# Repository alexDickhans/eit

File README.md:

# HIRO Group ERT Board V1

The name on the silkscreen is HIRO Group ERT Board V1. This board is a 16-electrode front end for a Raspberry Pi Pico W. J2 brings in the electrodes. Four analog switches connect those electrodes to a voltage measurement, a current source, and a current-return sense. A DAC and an op amp set the current. Two programmable-gain amplifiers and a two-channel ADC measure the voltage and the current. The Pico reads the ADC and sets the switch addresses and the gains.

Open `eit.kicad_pro` in KiCad 9. The schematic and the board were written by KiCad 9.0.

J2 is a 2×8 header, electrodes 0 through 15, with no electrode numbers on the silk. All four switches see the same electrodes. U6 selects the positive voltage electrode (its drain is `vin.+`, into U3). U8 selects the negative voltage electrode (`vin.?`, into U3). U11 selects the electrode that the current source drives (`current.out`). U10 selects the electrode that returns that current (`shunt.+`, into U4). Each switch enable pin is pulled to 3.3 V by a 10 k? resistor (R4 on U6, R13 on U8, R11 on U10, R12 on U11) and is not a Pico pin.

U9 is a 74HC595. Its serial input is Pico GPIO10, and its outputs address U10 and U11. U7 is the other 74HC595. Its serial input is GPIO11, and its outputs address U6 and U8. Both registers share SRCLK on GPIO13 and RCLK on GPIO12. Register clear is tied to 3.3 V, and output enable is tied to ground. Nothing has to be held at reset.

U3 and U4 are PGA281 amplifiers. U3 measures the electrode voltage. U4 measures the voltage across the 820 ? shunt R10. Both outputs go to U1, an ADS8354. Pico GPIO0 through GPIO4 set the U3 gain. GPIO5 through GPIO9 set the U4 gain.

U2 is a DAC80502. SPI2C (pin 5) and RSTSEL (pin 3) are tied to ground, so the part is in SPI mode. U5 is an OPA192. RN1 (four 100 k? resistors in one array) and RN2 (two 5 k? resistors in one array) are the resistors around that op amp. NT1 is a copper short from the ground end of R10 to GND. It is not a component.

## Pictures

Top of the board, USB edge up. The Pico (A1) is on the left and its USB connector faces the top edge. J1 is the 5-pin header just to the right of the Pico. J2 is the 16-pin header on the right. JP1 and JP2 are the open yellow solder jumpers near the top. U1, U5, U6, U8, U10, and U11 have no 3D model in the footprint, so those locations show the pads and the silkscreen outline. The Pico, the headers, the passives, D1, U2, U3, U4, U7, U9, RN1, and RN2 are the models from their footprints, sitting on the lands.

Bottom of the board, looking at the back, so left and right are swapped from the top photo. There are no parts on this side. The 2×8 set of holes on the left is J2. The five holes near the top are J1, and in this view the square pin-1 pad is the right-hand hole of that row. The four holes at the top right are the Pico USB shell holes.

Three-quarter view of the top, USB edge toward the lower left. The header pins and the Pico body are 3D models on their lands. The four empty outlines along the lower edge are U6, U8, U10, and U11, drawn as footprints because those packages have no 3D model. U1 and U5 are the same: pads and silk, not a package body.

Root sheet. The blocks are the power connector, the Pico, the current source, the voltage and current measurement, the switches, and J2.

Power sheet. J1 pins, in schematic order, are GND, +5V, +5VA, ?5VA, and +15V. R9 and R8 divide +5VA to make +2V5. The names GND, GNDA, and GNDD are one net.

Pico sheet. D1 is the MBR0540T1G from J1 +5V into VSYS. VBUS, RUN, and 3V3_EN are open.

Current source. U2, U5, RN1, RN2, the 820 ? shunt R10, the copper short NT1, and the open jumpers JP1 and JP2.

Measurement sheet. U3 is the voltage amplifier, U4 is the current amplifier, and U1 is the ADS8354.

Switch sheet. U6 is the positive voltage switch, U8 is the negative voltage switch, U11 is the current output, and U10 is the current return. U9 addresses U10 and U11. U7 addresses U6 and U8.

One switch, drawn for U6. U8, U10, and U11 use the same circuit. The drain (pin 28) is `vin.+` on U6, `vin.?` on U8, `shunt.+` on U10, and `current.out` on U11. S1 through S16 are electrodes 0 through 15.

Shift register U9. U7 is the same circuit, with serial data from GPIO11, and it drives U6 and U8.

J2 on the schematic. Pin 1 is electrode 7. On this drawing, pin 1 is at the bottom of the left column. On the board, pin 1 is the square pad at the top of the column closer to the middle of the board. The net is electrode 7 either way.

## Connectors and holes

Orient the board with the USB edge up, as in the top photo. There are no mounting holes and no test points. The boxes marked SN: and QC: are silkscreen only.

| Silk | What it is |
| --- | --- |
| J1 | 1×5 pin header, 2.54 mm. Power input. Pin 1 is the square pad, the left end. |
| J2 | 2×8 pin header, 2.54 mm. Electrodes. Pin 1 is the square pad at the top of the inner column (the column closer to the middle of the board). The silk does not number the electrodes. |
| JP1 | Open solder jumper. Left pad is GND, right pad is U2 VOUTB. Leave it open. Closing it shorts VOUTB to ground. |
| JP2 | Open solder jumper. Left pad is U2 VOUTA, right pad is GND. Leave it open. Closing it shorts VOUTA to ground. |
| A1 | Raspberry Pi Pico W. Pin 1 of the footprint is the left pin at the USB end (GPIO0). The USB connector faces the top edge. |
| D1 | SOD-123 diode. Pin 1 is the left end, the cathode band, on Pico VSYS. The right end is the anode, on J1 +5V. |
| D1, D2, D3 | Three 1.0 mm plated holes under the Pico footprint. They have no net. The module covers them once it is soldered. These are not the diode D1. |

J1, left to right. The silkscreen above the pins reads GND, +5V, +5VA, ?5VA, +15VA. The net on the last pin is +15V.

| J1 pin | Silkscreen | Net |
| --- | --- | --- |
| 1 | GND | GND |
| 2 | +5V | +5V |
| 3 | +5VA | +5VA |
| 4 | ?5VA | ?5VA |
| 5 | +15VA | +15V |

J2, with the USB edge up. The inner column is toward the middle of the board.

| Inner pin | Electrode | Outer pin | Electrode |
| --- | --- | --- | --- |
| 1 (top, square) | 7 | 2 | 15 |
| 3 | 6 | 4 | 14 |
| 5 | 5 | 6 | 13 |
| 7 | 4 | 8 | 12 |
| 9 | 3 | 10 | 11 |
| 11 | 2 | 12 | 10 |
| 13 | 1 | 14 | 9 |
| 15 (bottom) | 0 | 16 | 8 |

Pico pins that leave the module. Pin 1 is the top pin on the left edge.

| Pico pin | GPIO | Net |
| --- | --- | --- |
| 1 | GPIO0 | vgain0, U3 gain |
| 2 | GPIO1 | vgain1 |
| 4 | GPIO2 | vgain2 |
| 5 | GPIO3 | vgain3 |
| 6 | GPIO4 | vgain4 |
| 7 | GPIO5 | igain0, U4 gain |
| 9 | GPIO6 | igain1 |
| 10 | GPIO7 | igain2 |
| 11 | GPIO8 | igain3 |
| 12 | GPIO9 | igain4 |
| 14 | GPIO10 | U9 serial data |
| 15 | GPIO11 | U7 serial data |
| 16 | GPIO12 | shift-register RCLK |
| 17 | GPIO13 | shift-register SRCLK |
| 19 | GPIO14 | U2 chip select |
| 20 | GPIO15 | U1 chip select |
| 21 | GPIO16 | SPI MISO |
| 24 | GPIO18 | SPI clock |
| 25 | GPIO19 | SPI MOSI |
| 36 | 3V3 out | +3V3 |
| 39 | VSYS | cathode of D1 |
| 40 | VBUS | open |

GPIO17, GPIO20, GPIO21, GPIO22, GPIO26, GPIO27, GPIO28, ADC_VREF, RUN, and 3V3_EN are open on the board. The four holes beside the USB connector are non-plated holes in the Pico footprint (two 2.2 mm, two 1.85 mm) for the USB shell.

R4 and C38 are fitted. Their reference designators are hidden on the silkscreen, so the board does not print "R4" or "C38".

## Power

All board power comes in on J1. Pin 1, the square pad on the left, is ground. Supply +5V, +5VA, ?5VA, and +15V on the pins in the table above. +5VA is a separate pin from +5V. The board does not make one from the other.

There is no regulator, no charger, and no battery on this board. +3V3 is the Pico's own regulator, from VSYS, and it comes out on Pico pin 36. +2V5 is only the midpoint of R9 (10 k? from +5VA) and R8 (10 k? to GND). It is the output common-mode pin of U3 and U4. Do not use it to power anything.

D1 lets J1 +5V feed Pico VSYS and blocks the Pico from driving +5V back out of J1. The Pico USB connector does not power the Pico and does not power the analog rails, because VBUS is open. Plug in J1 +5V before expecting the Pico, the switches, or the ADC to run. +5VA, ?5VA, and +15V go straight to the analog parts, with no reverse protection. JP1 and JP2 must stay open.

## Manufacturing

Order a 6-layer, 1.6 mm board, 109.4 mm by 52.5 mm. Copper is 1 oz (0.035 mm) on every layer. F.Cu, In2.Cu, In3.Cu, and B.Cu are signal layers. In1.Cu and In4.Cu are ground planes. Mask is black and silk is white, as set in the stackup. The board file does not name a surface finish, and it does not call for impedance control.

The smallest trace is 0.15 mm, on F.Cu and In2.Cu. The smallest clearance in the design rules is 0.15 mm, on the electrode nets, and DRC reported no clearance errors. Vias are 0.6 mm pad / 0.3 mm drill, and 0.8 mm pad / 0.4 mm drill. Plated holes are 1.0 mm (J1, J2, and the three holes under the Pico) and one 0.20 mm hole in the U1 exposed pad. Non-plated holes are the four Pico USB shell holes. The copper-to-edge rule in the board is 0.5 mm, and DRC reported no edge violations.

Send `production/eit.zip`. It contains the six copper layers, both solder masks, both silkscreens, both paste layers, the board outline, and one Excellon drill file. Coordinates are absolute, in millimeters, and the soldermask is subtracted from the silk. The bottom paste file is empty because every part is on the top. The drill file includes the plated and the non-plated holes. Do not add a drill map or a separate non-plated drill file.

`production/bom.csv` is the parts list: Designator, Comment, Footprint, Qty, and LCSC Part #. Comment is the value printed in the schematic. JP1, JP2, and NT1 are left off on purpose. A1 has no LCSC number; buy a Raspberry Pi Pico W and fit it to the handsolder footprint. C6, C38, and C53 are 0.1 µF in 0402 under LCSC C1525. The other 0.1 µF 0402 parts are C343047. Both are 100 nF, 0402. RN1 is one 4-resistor array, 100 k? each (LCSC package 0603×4, footprint `R_Array_Convex_4x0612`). RN2 is one 2-resistor array, 5 k? each (LCSC package 0603×2, footprint `R_Array_Convex_2x0606`). R10 is an 820 ? resistor on a 0603 resistor footprint.

`production/position.csv` is the KiCad placement file for both sides, in millimeters. DNP parts are excluded, and so are JP1, JP2, NT1, and the two silk logos. The header is Designator, Val, Package, Mid X, Mid Y, Rotation, Layer. Y is negative, the same origin as the gerbers. Do not flip Y, and do not negate X. Every part is on the top, so the Layer column reads `top`. The rotations are KiCad's. Check the assembler's placement preview before paying.

Parts that are easy to rotate the wrong way, with the USB edge as the top edge:

| Part | Pin 1 |
| --- | --- |
| A1 Pico W | Left pin at the USB end. The USB connector faces the top edge. |
| D1 | Left end. That end is the cathode band, on VSYS. |
| J1 | Square pad, left end. |
| J2 | Square pad, top of the inner column. |
| U1 | Corner toward the bottom-left of the package. |
| U2 | Corner toward the bottom-right of the package. |
| U3 | Corner toward the top-left of the package. |
| U4 | Corner toward the top-right of the package. |
| U5 | Lower pin on the left side of the SOT-23. |
| U6, U8, U10, U11 | Bottom-left corner of each TSSOP. The silkscreen outline is the footprint, not a drawn module. |
| U7, U9 | Bottom-right corner of each SOIC. |
| RN1 | Left end, the pad closer to the USB edge. |
| RN2 | Pad closer to the USB edge. |

## Design files

| Path | What it is |
| --- | --- |
| `eit.kicad_pro` | KiCad 9 project |
| `eit.kicad_sch` | Root schematic. The other `.kicad_sch` files are the sheets. |
| `eit.kicad_pcb` | Board |
| `production/eit.zip` | Gerbers and drill for this revision |
| `production/bom.csv` | Bill of materials |
| `production/position.csv` | Placement, both sides, millimeters |
| `images/` | The pictures above |

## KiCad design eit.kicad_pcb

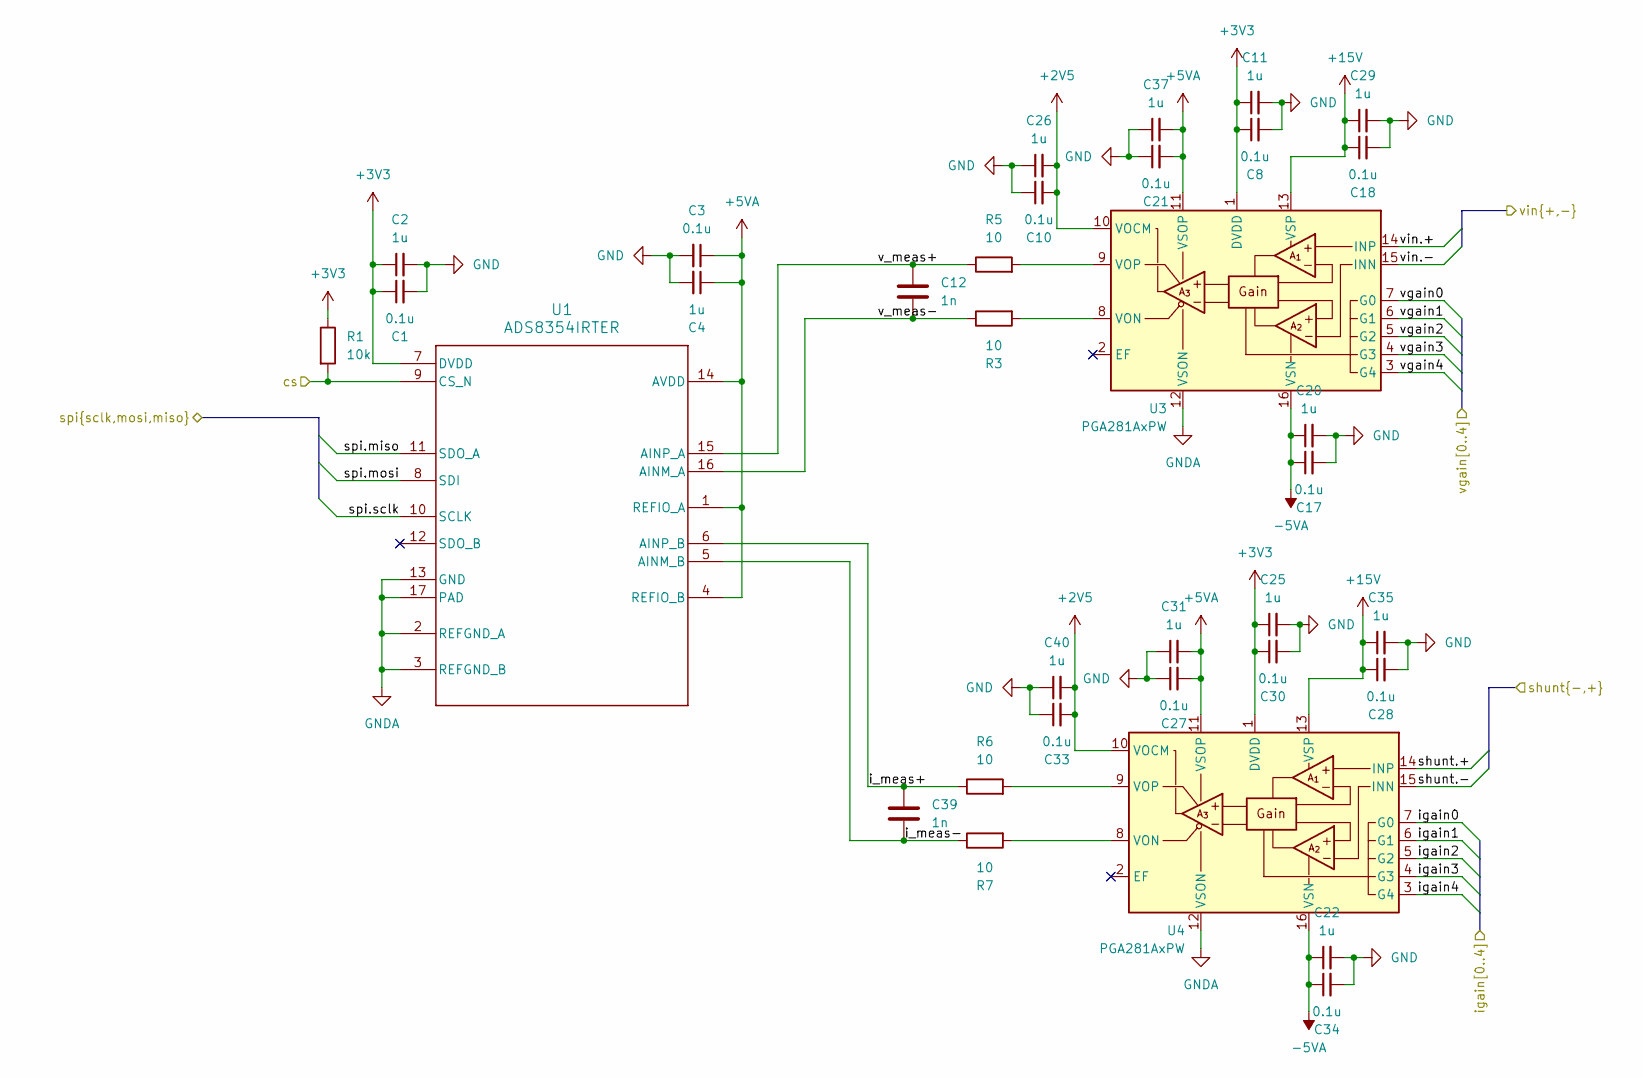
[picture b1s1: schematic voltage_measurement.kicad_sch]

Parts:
C1, C3, C8, C10, C17, C18, C21, C27, C28, C30, C33, C34: 0.1u; C_0402_1005Metric; LCSC Part # C343047
C2, C4, C11, C20, C22, C25, C26, C29, C31, C35, C37, C40: 1u; C_0603_1608Metric; LCSC Part # C342956
C12, C39: 1n; C_0402_1005Metric; LCSC Part # C1523
R1: 10k; R_0402_1005Metric; LCSC Part # C25744
R3, R5, R6, R7: 10; R_0402_1005Metric; LCSC Part # C25077
U1: ADS8354IRTER; RTE0016D; LCSC Part # C2670004
U3, U4: PGA281AxPW; TSSOP-16_4.4x5mm_P0.65mm; LCSC Part # C69359

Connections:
+2V5: C10.2, C26.2, C33.2, C40.2, U3.10 (VOCM), U4.10 (VOCM); also elsewhere on the board
+3V3: C1.1, C2.1, C8.1, C11.1, C25.1, C30.1, R1.1, U1.7 (DVDD), U3.1 (DVDD), U4.1 (DVDD); also elsewhere on the board
+5VA: C3.1, C4.1, C21.2, C27.2, C31.2, C37.2, U1.1 (REFIO_A), U1.4 (REFIO_B), U1.14 (AVDD), U3.11 (VSOP), U4.11 (VSOP); also elsewhere on the board
+15V: C18.1, C28.1, C29.1, C35.1, U3.13 (VSP), U4.13 (VSP); also elsewhere on the board
-5VA: C17.1, C20.1, C22.1, C34.1, U3.16 (VSN), U4.16 (VSN); also elsewhere on the board
/Current Injection/shunt.+: U4.14 (INP); also elsewhere on the board
/Current Injection/shunt.-: U4.15 (INN); also elsewhere on the board
/Current Injection/spi.miso: U1.11 (SDO_A); also elsewhere on the board
/Current Injection/spi.mosi: U1.8 (SDI); also elsewhere on the board
/Current Injection/spi.sclk: U1.10 (SCLK); also elsewhere on the board
/Microcontroller/adc_cs: R1.2, U1.9 (CS_N); also elsewhere on the board
/Microcontroller/igain0: U4.7 (G0); also elsewhere on the board
/Microcontroller/igain1: U4.6 (G1); also elsewhere on the board
/Microcontroller/igain2: U4.5 (G2); also elsewhere on the board
/Microcontroller/igain3: U4.4 (G3); also elsewhere on the board
/Microcontroller/igain4: U4.3 (G4); also elsewhere on the board
/Microcontroller/vgain0: U3.7 (G0); also elsewhere on the board
/Microcontroller/vgain1: U3.6 (G1); also elsewhere on the board
/Microcontroller/vgain2: U3.5 (G2); also elsewhere on the board
/Microcontroller/vgain3: U3.4 (G3); also elsewhere on the board
/Microcontroller/vgain4: U3.3 (G4); also elsewhere on the board
/Mux/vin.+: U3.14 (INP); also elsewhere on the board
/Mux/vin.-: U3.15 (INN); also elsewhere on the board
/Voltage Measurement/i_meas+: C39.1, R6.1, U1.6 (AINP_B)
/Voltage Measurement/i_meas-: C39.2, R7.1, U1.5 (AINM_B)
/Voltage Measurement/v_meas+: C12.1, R5.1, U1.15 (AINP_A)
/Voltage Measurement/v_meas-: C12.2, R3.1, U1.16 (AINM_A)
GND: C1.2, C2.2, C3.2, C4.2, C8.2, C10.1, C11.2, C17.2, C18.2, C20.2, C21.1, C22.2, C25.2, C26.1, C27.1, C28.2, C29.2, C30.2, C31.1, C33.1, C34.2, C35.2, C37.1, C40.1, U1.2 (REFGND_A), U1.3 (REFGND_B), U1.13 (GND), U1.17 (PAD), U3.12 (VSON), U4.12 (VSON); also elsewhere on the board
unnamed: R3.2, U3.8 (VON)
unnamed: R5.2, U3.9 (VOP)
unnamed: R7.2, U4.8 (VON)
unnamed: R6.2, U4.9 (VOP)

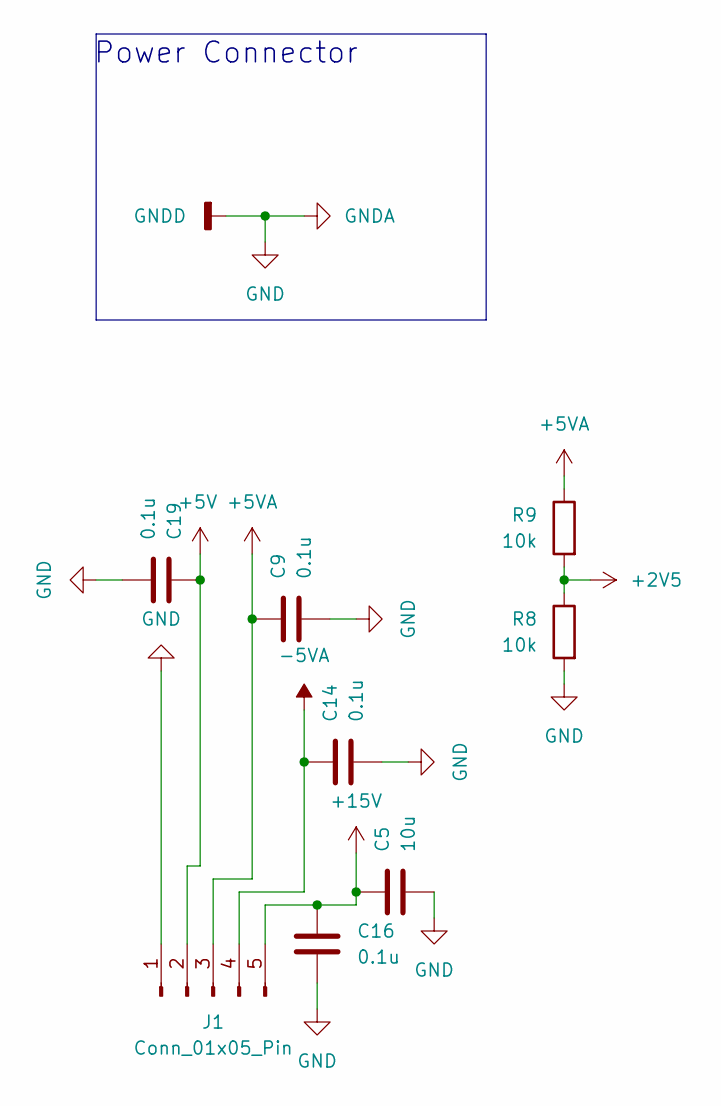
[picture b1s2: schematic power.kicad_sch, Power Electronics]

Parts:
C5: 10u; C_1210_3225Metric; LCSC Part # C18739
C9, C14, C16, C19: 0.1u; C_0603_1608Metric; LCSC Part # C14663
J1: Conn_01x05_Pin; PinHeader_1x05_P2.54mm_Vertical; LCSC Part # C188243
R8, R9: 10k; R_0402_1005Metric; LCSC Part # C25744

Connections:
+2V5: R8.1, R9.2; also elsewhere on the board
+5V: C19.2, J1.2; also elsewhere on the board
+5VA: C9.2, J1.3, R9.1; also elsewhere on the board
+15V: C5.1, C16.2, J1.5; also elsewhere on the board
-5VA: C14.2, J1.4; also elsewhere on the board
GND: C5.2, C9.1, C14.1, C16.1, C19.1, J1.1, R8.2; also elsewhere on the board

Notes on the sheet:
Power Connector

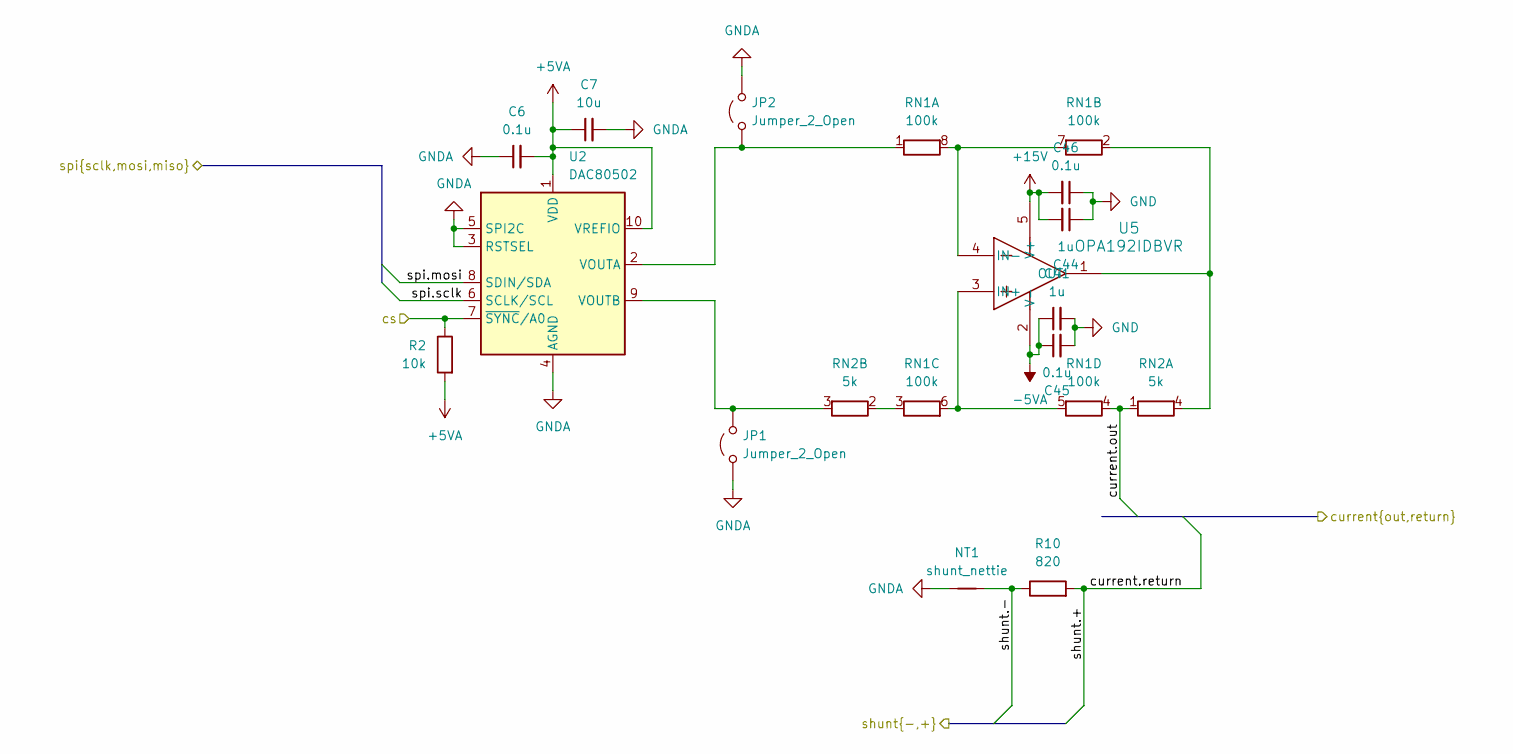
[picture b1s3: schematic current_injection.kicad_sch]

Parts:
C6: 0.1u; C_0402_1005Metric; LCSC Part # C1525
C7: 10u; C_0805_2012Metric; LCSC Part # C95841
C41, C44: 1u; C_0603_1608Metric; LCSC Part # C342956
C45, C46: 0.1u; C_0402_1005Metric; LCSC Part # C343047
JP1, JP2: Jumper_2_Open; SolderJumper-2_P1.3mm_Open_RoundedPad1.0x1.5mm
NT1: shunt_nettie; NetTie-2_SMD_Pad0.5mm
R2: 10k; R_0402_1005Metric; LCSC Part # C25744
R10: 820; R_0603_1608Metric; LCSC Part # C19700783
RN1: 100k; R_Array_Convex_4x0612; LCSC Part # C1731595
RN2: 5k; R_Array_Convex_2x0606; LCSC Part # C1731135
U2: DAC80502; Texas_DRX_WSON-10_2.5x2.5mm_P0.5mm; LCSC Part # C1880990
U5: OPA192IDBVR; DBV0005A_N; LCSC Part # C139648

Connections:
+5VA: C6.2, C7.1, R2.2, U2.1 (VDD), U2.10 (VREFIO); also elsewhere on the board
+15V: C44.2, C46.2, U5.5 (V+); also elsewhere on the board
-5VA: C41.1, C45.1, U5.2 (V-); also elsewhere on the board
/Current Injection/cs: R2.1, U2.7 (~SYNC/A0); also elsewhere on the board
/Current Injection/current.out: RN1.4 (R4.1), RN2.1 (R1.1); also elsewhere on the board
/Current Injection/shunt.+: R10.2; also elsewhere on the board
/Current Injection/shunt.-: NT1.2, R10.1; also elsewhere on the board
/Current Injection/spi.mosi: U2.8 (SDIN/SDA); also elsewhere on the board
/Current Injection/spi.sclk: U2.6 (SCLK/SCL); also elsewhere on the board
GND: C6.1, C7.2, C41.2, C44.1, C45.2, C46.1, JP1.1 (A), JP2.2 (B), NT1.1, U2.3 (RSTSEL), U2.4 (AGND), U2.5 (SPI2C); also elsewhere on the board
unnamed: JP1.2 (B), RN2.3 (R2.2), U2.9 (VOUTB)
unnamed: JP2.1 (A), RN1.1 (R1.1), U2.2 (VOUTA)
unnamed: RN1.7 (R2.2), RN1.8 (R1.2), U5.4 (IN-)
unnamed: RN1.2 (R2.1), RN2.4 (R1.2), U5.1 (OUT)
unnamed: RN1.3 (R3.1), RN2.2 (R2.1)
unnamed: RN1.5 (R4.2), RN1.6 (R3.2), U5.3 (IN+)

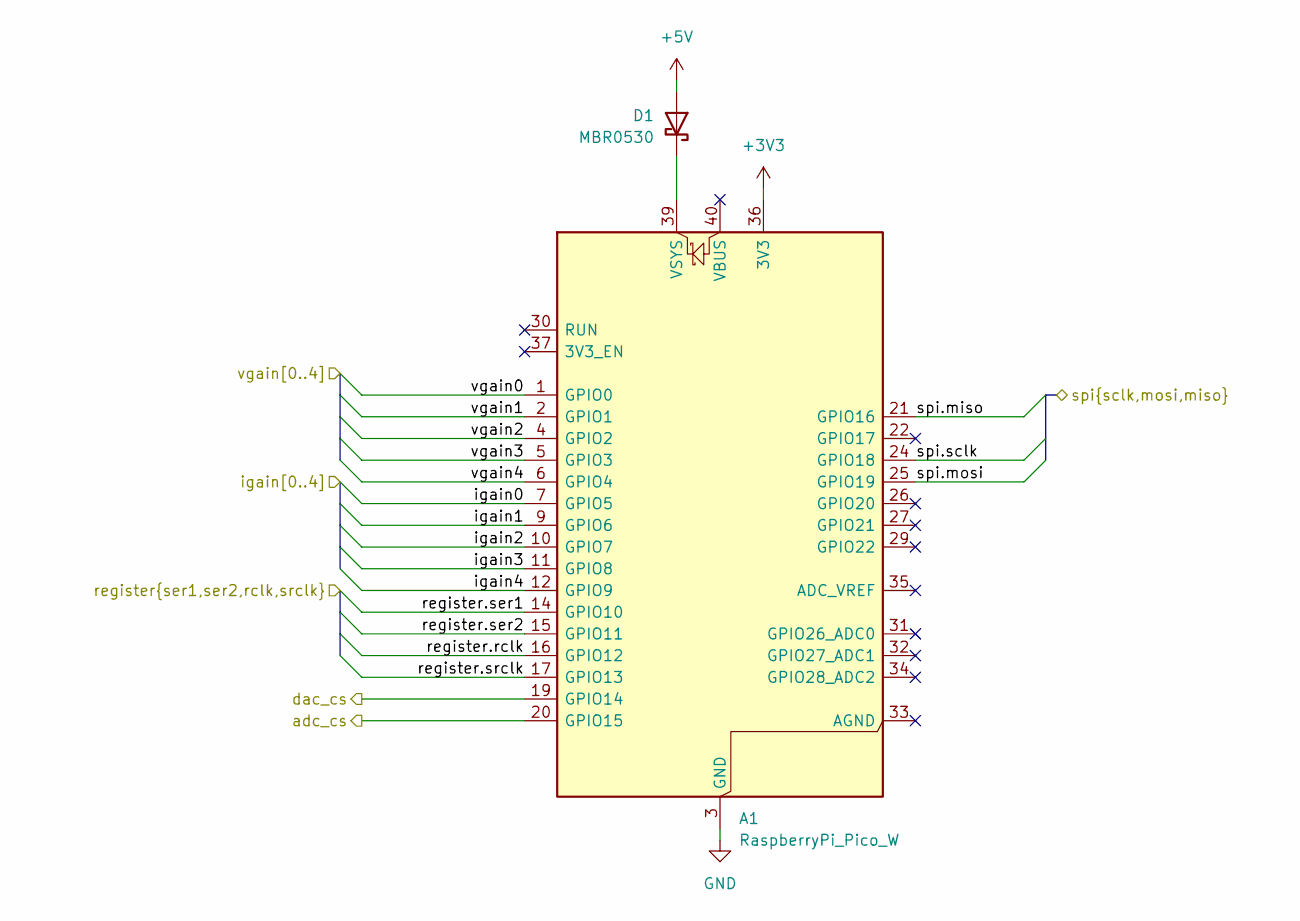
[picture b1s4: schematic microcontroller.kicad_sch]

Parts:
A1: RaspberryPi_Pico_W; RaspberryPi_Pico_W_SMD_HandSolder
D1: MBR0530; D_SOD-123; LCSC Part # C21353

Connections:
+3V3: A1.36 (3V3); also elsewhere on the board
+5V: D1.2 (A); also elsewhere on the board
/Current Injection/cs: A1.19 (GPIO14); also elsewhere on the board
/Current Injection/spi.miso: A1.21 (GPIO16); also elsewhere on the board
/Current Injection/spi.mosi: A1.25 (GPIO19); also elsewhere on the board
/Current Injection/spi.sclk: A1.24 (GPIO18); also elsewhere on the board
/Microcontroller/adc_cs: A1.20 (GPIO15); also elsewhere on the board
/Microcontroller/igain0: A1.7 (GPIO5); also elsewhere on the board
/Microcontroller/igain1: A1.9 (GPIO6); also elsewhere on the board
/Microcontroller/igain2: A1.10 (GPIO7); also elsewhere on the board
/Microcontroller/igain3: A1.11 (GPIO8); also elsewhere on the board
/Microcontroller/igain4: A1.12 (GPIO9); also elsewhere on the board
/Microcontroller/register.rclk: A1.16 (GPIO12); also elsewhere on the board
/Microcontroller/register.ser1: A1.14 (GPIO10); also elsewhere on the board
/Microcontroller/register.ser2: A1.15 (GPIO11); also elsewhere on the board
/Microcontroller/register.srclk: A1.17 (GPIO13); also elsewhere on the board
/Microcontroller/vgain0: A1.1 (GPIO0); also elsewhere on the board
/Microcontroller/vgain1: A1.2 (GPIO1); also elsewhere on the board
/Microcontroller/vgain2: A1.4 (GPIO2); also elsewhere on the board
/Microcontroller/vgain3: A1.5 (GPIO3); also elsewhere on the board
/Microcontroller/vgain4: A1.6 (GPIO4); also elsewhere on the board
GND: A1.3 (GND), A1.8 (GND), A1.13 (GND), A1.18 (GND), A1.23 (GND), A1.28 (GND), A1.38 (GND); also elsewhere on the board
unnamed: A1.39 (VSYS), D1.1 (K)

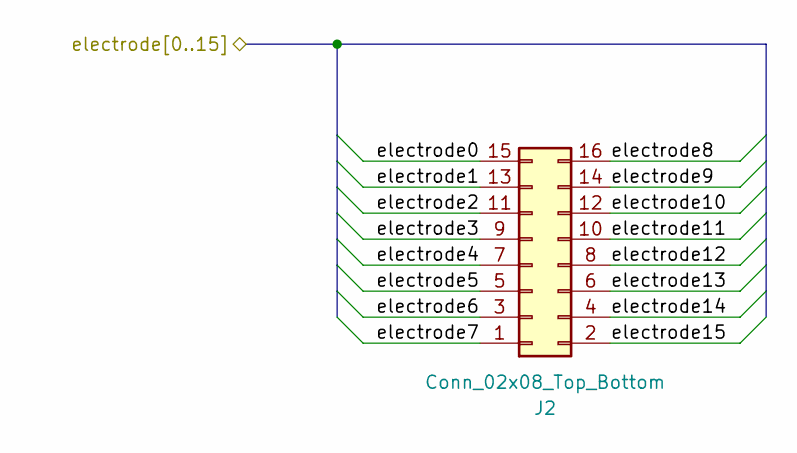
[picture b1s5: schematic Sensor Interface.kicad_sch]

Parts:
J2: Conn_02x08_Top_Bottom; PinHeader_2x08_P2.54mm_Vertical; LCSC Part # C68234

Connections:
/Mux/electrode0: J2.15; also elsewhere on the board
/Mux/electrode1: J2.13; also elsewhere on the board
/Mux/electrode2: J2.11; also elsewhere on the board
/Mux/electrode3: J2.9; also elsewhere on the board
/Mux/electrode4: J2.7; also elsewhere on the board
/Mux/electrode5: J2.5; also elsewhere on the board
/Mux/electrode6: J2.3; also elsewhere on the board
/Mux/electrode7: J2.1; also elsewhere on the board
/Mux/electrode8: J2.16; also elsewhere on the board
/Mux/electrode9: J2.14; also elsewhere on the board
/Mux/electrode10: J2.12; also elsewhere on the board
/Mux/electrode11: J2.10; also elsewhere on the board
/Mux/electrode12: J2.8; also elsewhere on the board
/Mux/electrode13: J2.6; also elsewhere on the board
/Mux/electrode14: J2.4; also elsewhere on the board
/Mux/electrode15: J2.2; also elsewhere on the board

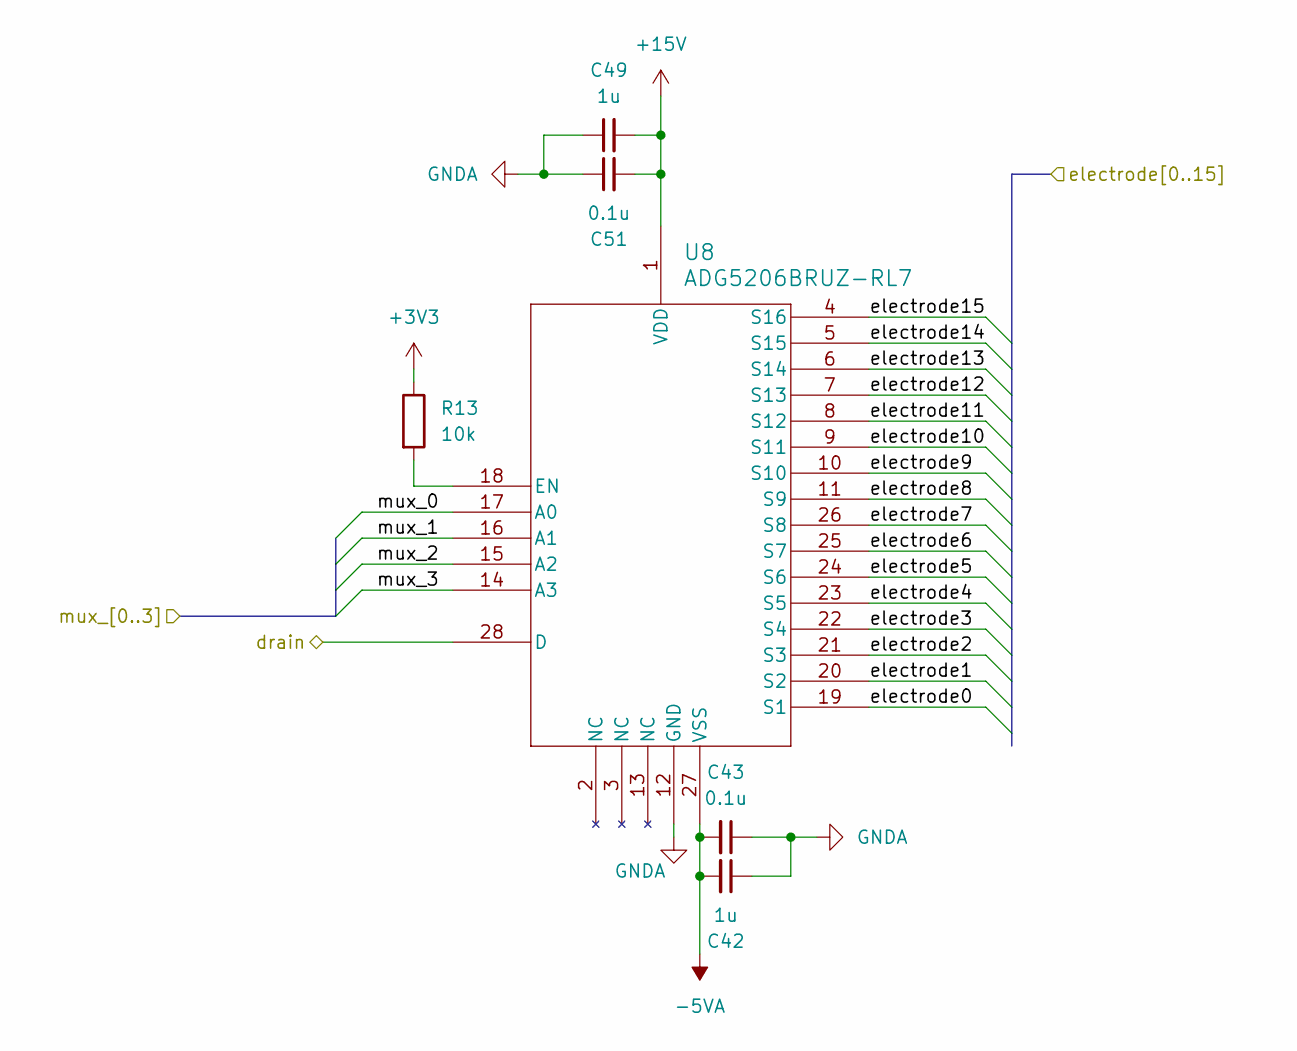
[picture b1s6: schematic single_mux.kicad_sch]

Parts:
C42, C49: 1u; C_0603_1608Metric; LCSC Part # C342956
C43, C51: 0.1u; C_0402_1005Metric; LCSC Part # C343047
R13: 10k; R_0402_1005Metric; LCSC Part # C25744
U8: ADG5206BRUZ-RL7; RU_28_ADI; LCSC Part # C657435

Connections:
+3V3: R13.1; also elsewhere on the board
+15V: C49.2, C51.2, U8.1 (VDD); also elsewhere on the board
-5VA: C42.2, C43.2, U8.27 (VSS); also elsewhere on the board
/Mux/Shift Register1/mux2_0: U8.17 (A0); also elsewhere on the board
/Mux/Shift Register1/mux2_1: U8.16 (A1); also elsewhere on the board
/Mux/Shift Register1/mux2_2: U8.15 (A2); also elsewhere on the board
/Mux/Shift Register1/mux2_3: U8.14 (A3); also elsewhere on the board
/Mux/electrode0: U8.19 (S1); also elsewhere on the board
/Mux/electrode1: U8.20 (S2); also elsewhere on the board
/Mux/electrode2: U8.21 (S3); also elsewhere on the board
/Mux/electrode3: U8.22 (S4); also elsewhere on the board
/Mux/electrode4: U8.23 (S5); also elsewhere on the board
/Mux/electrode5: U8.24 (S6); also elsewhere on the board
/Mux/electrode6: U8.25 (S7); also elsewhere on the board
/Mux/electrode7: U8.26 (S8); also elsewhere on the board
/Mux/electrode8: U8.11 (S9); also elsewhere on the board
/Mux/electrode9: U8.10 (S10); also elsewhere on the board
/Mux/electrode10: U8.9 (S11); also elsewhere on the board
/Mux/electrode11: U8.8 (S12); also elsewhere on the board
/Mux/electrode12: U8.7 (S13); also elsewhere on the board
/Mux/electrode13: U8.6 (S14); also elsewhere on the board
/Mux/electrode14: U8.5 (S15); also elsewhere on the board
/Mux/electrode15: U8.4 (S16); also elsewhere on the board
/Mux/vin.-: U8.28 (D); also elsewhere on the board
GND: C42.1, C43.1, C49.1, C51.1, U8.12 (GND); also elsewhere on the board
unnamed: R13.2, U8.18 (EN)

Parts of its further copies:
C13, C32, C36, C48, C52, C54: 0.1u; C_0402_1005Metric; LCSC Part # C343047
C15, C23, C24, C47, C50, C55: 1u; C_0603_1608Metric; LCSC Part # C342956
R4, R11, R12: 10k; R_0402_1005Metric; LCSC Part # C25744
U6, U10, U11: ADG5206BRUZ-RL7; RU_28_ADI; LCSC Part # C657435

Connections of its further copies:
+3V3: R4.1, R11.1, R12.1; also elsewhere on the board
+15V: C47.2, C48.2, C50.2, C52.2, C54.2, C55.2, U6.1 (VDD), U10.1 (VDD), U11.1 (VDD); also elsewhere on the board
-5VA: C13.2, C15.2, C23.2, C24.2, C32.2, C36.2, U6.27 (VSS), U10.27 (VSS), U11.27 (VSS); also elsewhere on the board
/Current Injection/current.out: U11.28 (D); also elsewhere on the board
/Current Injection/shunt.+: U10.28 (D); also elsewhere on the board
/Mux/Shift Register1/mux1_0: U6.17 (A0); also elsewhere on the board
/Mux/Shift Register1/mux1_1: U6.16 (A1); also elsewhere on the board
/Mux/Shift Register1/mux1_2: U6.15 (A2); also elsewhere on the board
/Mux/Shift Register1/mux1_3: U6.14 (A3); also elsewhere on the board
/Mux/Shift Register/mux1_0: U10.17 (A0); also elsewhere on the board
/Mux/Shift Register/mux1_1: U10.16 (A1); also elsewhere on the board
/Mux/Shift Register/mux1_2: U10.15 (A2); also elsewhere on the board
/Mux/Shift Register/mux1_3: U10.14 (A3); also elsewhere on the board
/Mux/Shift Register/mux2_0: U11.17 (A0); also elsewhere on the board
/Mux/Shift Register/mux2_1: U11.16 (A1); also elsewhere on the board
/Mux/Shift Register/mux2_2: U11.15 (A2); also elsewhere on the board
/Mux/Shift Register/mux2_3: U11.14 (A3); also elsewhere on the board
/Mux/electrode0: U6.19 (S1), U10.19 (S1), U11.19 (S1); also elsewhere on the board
/Mux/electrode1: U6.20 (S2), U10.20 (S2), U11.20 (S2); also elsewhere on the board
/Mux/electrode2: U6.21 (S3), U10.21 (S3), U11.21 (S3); also elsewhere on the board
/Mux/electrode3: U6.22 (S4), U10.22 (S4), U11.22 (S4); also elsewhere on the board
/Mux/electrode4: U6.23 (S5), U10.23 (S5), U11.23 (S5); also elsewhere on the board
/Mux/electrode5: U6.24 (S6), U10.24 (S6), U11.24 (S6); also elsewhere on the board
/Mux/electrode6: U6.25 (S7), U10.25 (S7), U11.25 (S7); also elsewhere on the board
/Mux/electrode7: U6.26 (S8), U10.26 (S8), U11.26 (S8); also elsewhere on the board
/Mux/electrode8: U6.11 (S9), U10.11 (S9), U11.11 (S9); also elsewhere on the board
/Mux/electrode9: U6.10 (S10), U10.10 (S10), U11.10 (S10); also elsewhere on the board
/Mux/electrode10: U6.9 (S11), U10.9 (S11), U11.9 (S11); also elsewhere on the board
/Mux/electrode11: U6.8 (S12), U10.8 (S12), U11.8 (S12); also elsewhere on the board
/Mux/electrode12: U6.7 (S13), U10.7 (S13), U11.7 (S13); also elsewhere on the board
/Mux/electrode13: U6.6 (S14), U10.6 (S14), U11.6 (S14); also elsewhere on the board
/Mux/electrode14: U6.5 (S15), U10.5 (S15), U11.5 (S15); also elsewhere on the board
/Mux/electrode15: U6.4 (S16), U10.4 (S16), U11.4 (S16); also elsewhere on the board
/Mux/vin.+: U6.28 (D); also elsewhere on the board
GND: C13.1, C15.1, C23.1, C24.1, C32.1, C36.1, C47.1, C48.1, C50.1, C52.1, C54.1, C55.1, U6.12 (GND), U10.12 (GND), U11.12 (GND); also elsewhere on the board
unnamed: R4.2, U6.18 (EN)
unnamed: R11.2, U10.18 (EN)
unnamed: R12.2, U11.18 (EN)

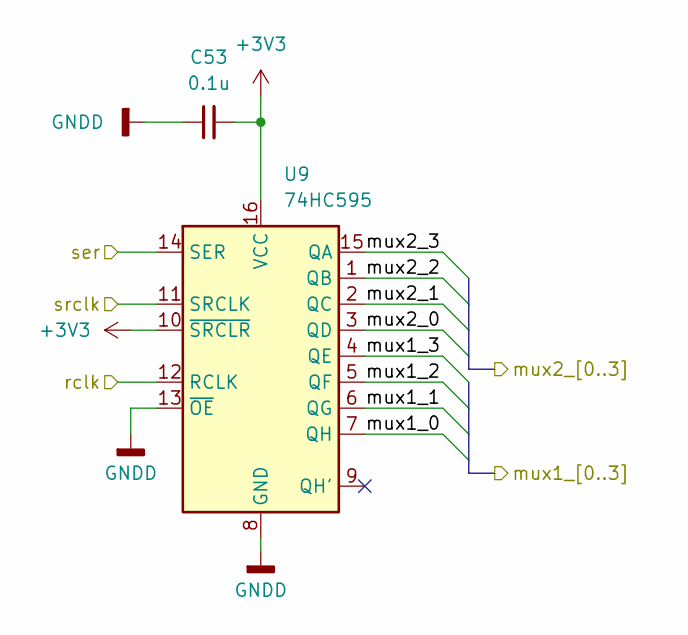
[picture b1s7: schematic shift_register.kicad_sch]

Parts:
C53: 0.1u; C_0402_1005Metric; LCSC Part # C1525
U9: 74HC595; SOIC-16_3.9x9.9mm_P1.27mm; LCSC Part # C10092

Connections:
+3V3: C53.2, U9.10 (~SRCLR), U9.16 (VCC); also elsewhere on the board
/Microcontroller/register.rclk: U9.12 (RCLK); also elsewhere on the board
/Microcontroller/register.ser1: U9.14 (SER); also elsewhere on the board
/Microcontroller/register.srclk: U9.11 (SRCLK); also elsewhere on the board
/Mux/Shift Register/mux1_0: U9.7 (QH); also elsewhere on the board
/Mux/Shift Register/mux1_1: U9.6 (QG); also elsewhere on the board
/Mux/Shift Register/mux1_2: U9.5 (QF); also elsewhere on the board
/Mux/Shift Register/mux1_3: U9.4 (QE); also elsewhere on the board
/Mux/Shift Register/mux2_0: U9.3 (QD); also elsewhere on the board
/Mux/Shift Register/mux2_1: U9.2 (QC); also elsewhere on the board
/Mux/Shift Register/mux2_2: U9.1 (QB); also elsewhere on the board
/Mux/Shift Register/mux2_3: U9.15 (QA); also elsewhere on the board
GND: C53.1, U9.8 (GND), U9.13 (~OE); also elsewhere on the board

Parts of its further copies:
C38: 0.1u; C_0402_1005Metric; LCSC Part # C1525
U7: 74HC595; SOIC-16_3.9x9.9mm_P1.27mm; LCSC Part # C10092

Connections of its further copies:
+3V3: C38.2, U7.10 (~SRCLR), U7.16 (VCC); also elsewhere on the board
/Microcontroller/register.rclk: U7.12 (RCLK); also elsewhere on the board
/Microcontroller/register.ser2: U7.14 (SER); also elsewhere on the board
/Microcontroller/register.srclk: U7.11 (SRCLK); also elsewhere on the board
/Mux/Shift Register1/mux1_0: U7.7 (QH); also elsewhere on the board
/Mux/Shift Register1/mux1_1: U7.6 (QG); also elsewhere on the board
/Mux/Shift Register1/mux1_2: U7.5 (QF); also elsewhere on the board
/Mux/Shift Register1/mux1_3: U7.4 (QE); also elsewhere on the board
/Mux/Shift Register1/mux2_0: U7.3 (QD); also elsewhere on the board
/Mux/Shift Register1/mux2_1: U7.2 (QC); also elsewhere on the board
/Mux/Shift Register1/mux2_2: U7.1 (QB); also elsewhere on the board
/Mux/Shift Register1/mux2_3: U7.15 (QA); also elsewhere on the board
GND: C38.1, U7.8 (GND), U7.13 (~OE); also elsewhere on the board

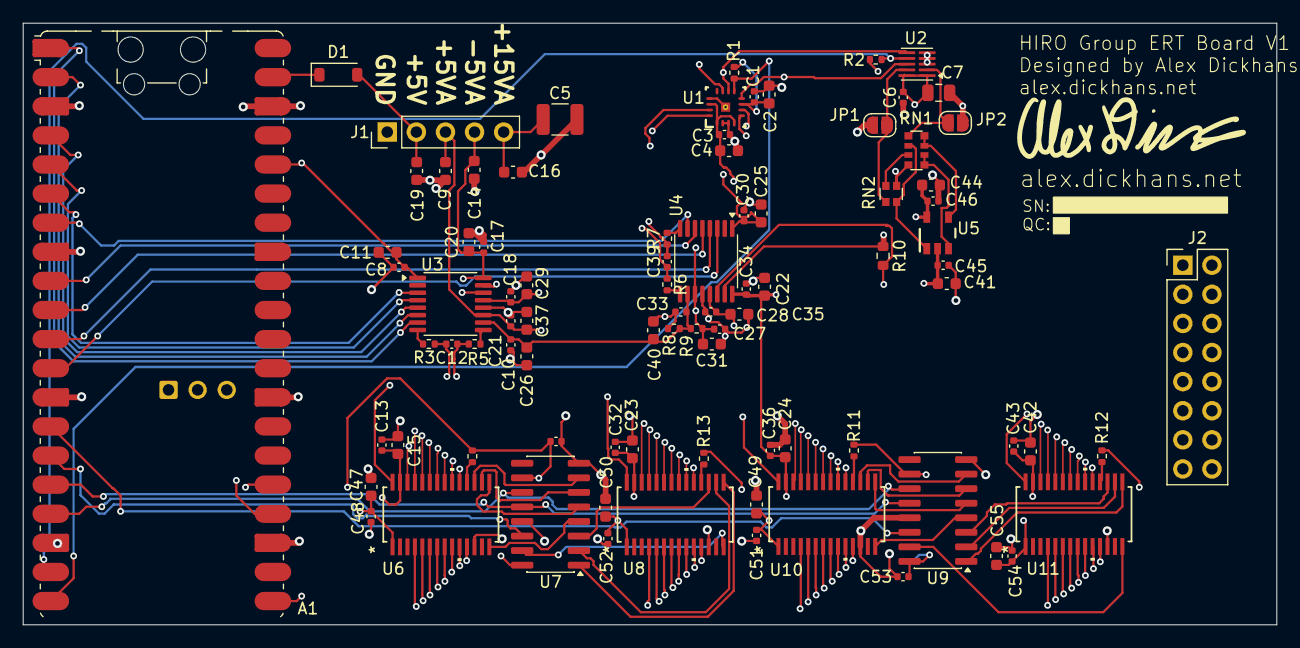
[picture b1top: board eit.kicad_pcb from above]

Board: 6 copper layers, 109.4 x 52.5 mm, 88 parts (0 on the bottom side), 82 nets.

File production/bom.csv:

"Designator","Comment","Footprint","Qty","LCSC Part #"
"A1","RaspberryPi_Pico_W","Module:RaspberryPi_Pico_W_SMD_HandSolder","1",""
"C1,C3,C8,C10,C13,C17,C18,C21,C27,C28,C30,C32,C33,C34,C36,C43,C45,C46,C48,C51,C52,C54","0.1u","Capacitor_SMD:C_0402_1005Metric","22","C343047"
"C2,C4,C11,C15,C20,C22,C23,C24,C25,C26,C29,C31,C35,C37,C40,C41,C42,C44,C47,C49,C50,C55","1u","Capacitor_SMD:C_0603_1608Metric","22","C342956"
"C5","10u","Capacitor_SMD:C_1210_3225Metric","1","C18739"
"C6,C38,C53","0.1u","Capacitor_SMD:C_0402_1005Metric","3","C1525"
"C7","10u","Capacitor_SMD:C_0805_2012Metric","1","C95841"
"C9,C14,C16,C19","0.1u","Capacitor_SMD:C_0603_1608Metric","4","C14663"
"C12,C39","1n","Capacitor_SMD:C_0402_1005Metric","2","C1523"
"D1","MBR0540T1G","Diode_SMD:D_SOD-123","1","C21353"
"J1","Conn_01x05_Pin","Connector_PinHeader_2.54mm:PinHeader_1x05_P2.54mm_Vertical","1","C188243"
"J2","Conn_02x08_Top_Bottom","Connector_PinHeader_2.54mm:PinHeader_2x08_P2.54mm_Vertical","1","C68234"
"R1,R2,R4,R8,R9,R11,R12,R13","10k","Resistor_SMD:R_0402_1005Metric","8","C25744"
"R3,R5,R6,R7","10","Resistor_SMD:R_0402_1005Metric","4","C25077"
"R10","820","Resistor_SMD:R_0603_1608Metric","1","C19700783"
"RN1","100k","Resistor_SMD:R_Array_Convex_4x0612","1","C1731595"
"RN2","5k","Resistor_SMD:R_Array_Convex_2x0606","1","C1731135"
"U1","ADS8354IRTER","ADS8354:RTE0016D","1","C2670004"
"U2","DAC80502","Package_SON:Texas_DRX_WSON-10_2.5x2.5mm_P0.5mm","1","C1880990"
"U3,U4","PGA281AxPW","Package_SO:TSSOP-16_4.4x5mm_P0.65mm","2","C69359"
"U5","OPA192IDBVR","OPA192:DBV0005A_N","1","C139648"
"U6,U8,U10,U11","ADG5206BRUZ-RL7","ADG5206:RU_28_ADI","4","C657435"
"U7,U9","74HC595","Package_SO:SOIC-16_3.9x9.9mm_P1.27mm","2","C10092"

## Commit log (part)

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2026-05-09 Ready to start Layout
